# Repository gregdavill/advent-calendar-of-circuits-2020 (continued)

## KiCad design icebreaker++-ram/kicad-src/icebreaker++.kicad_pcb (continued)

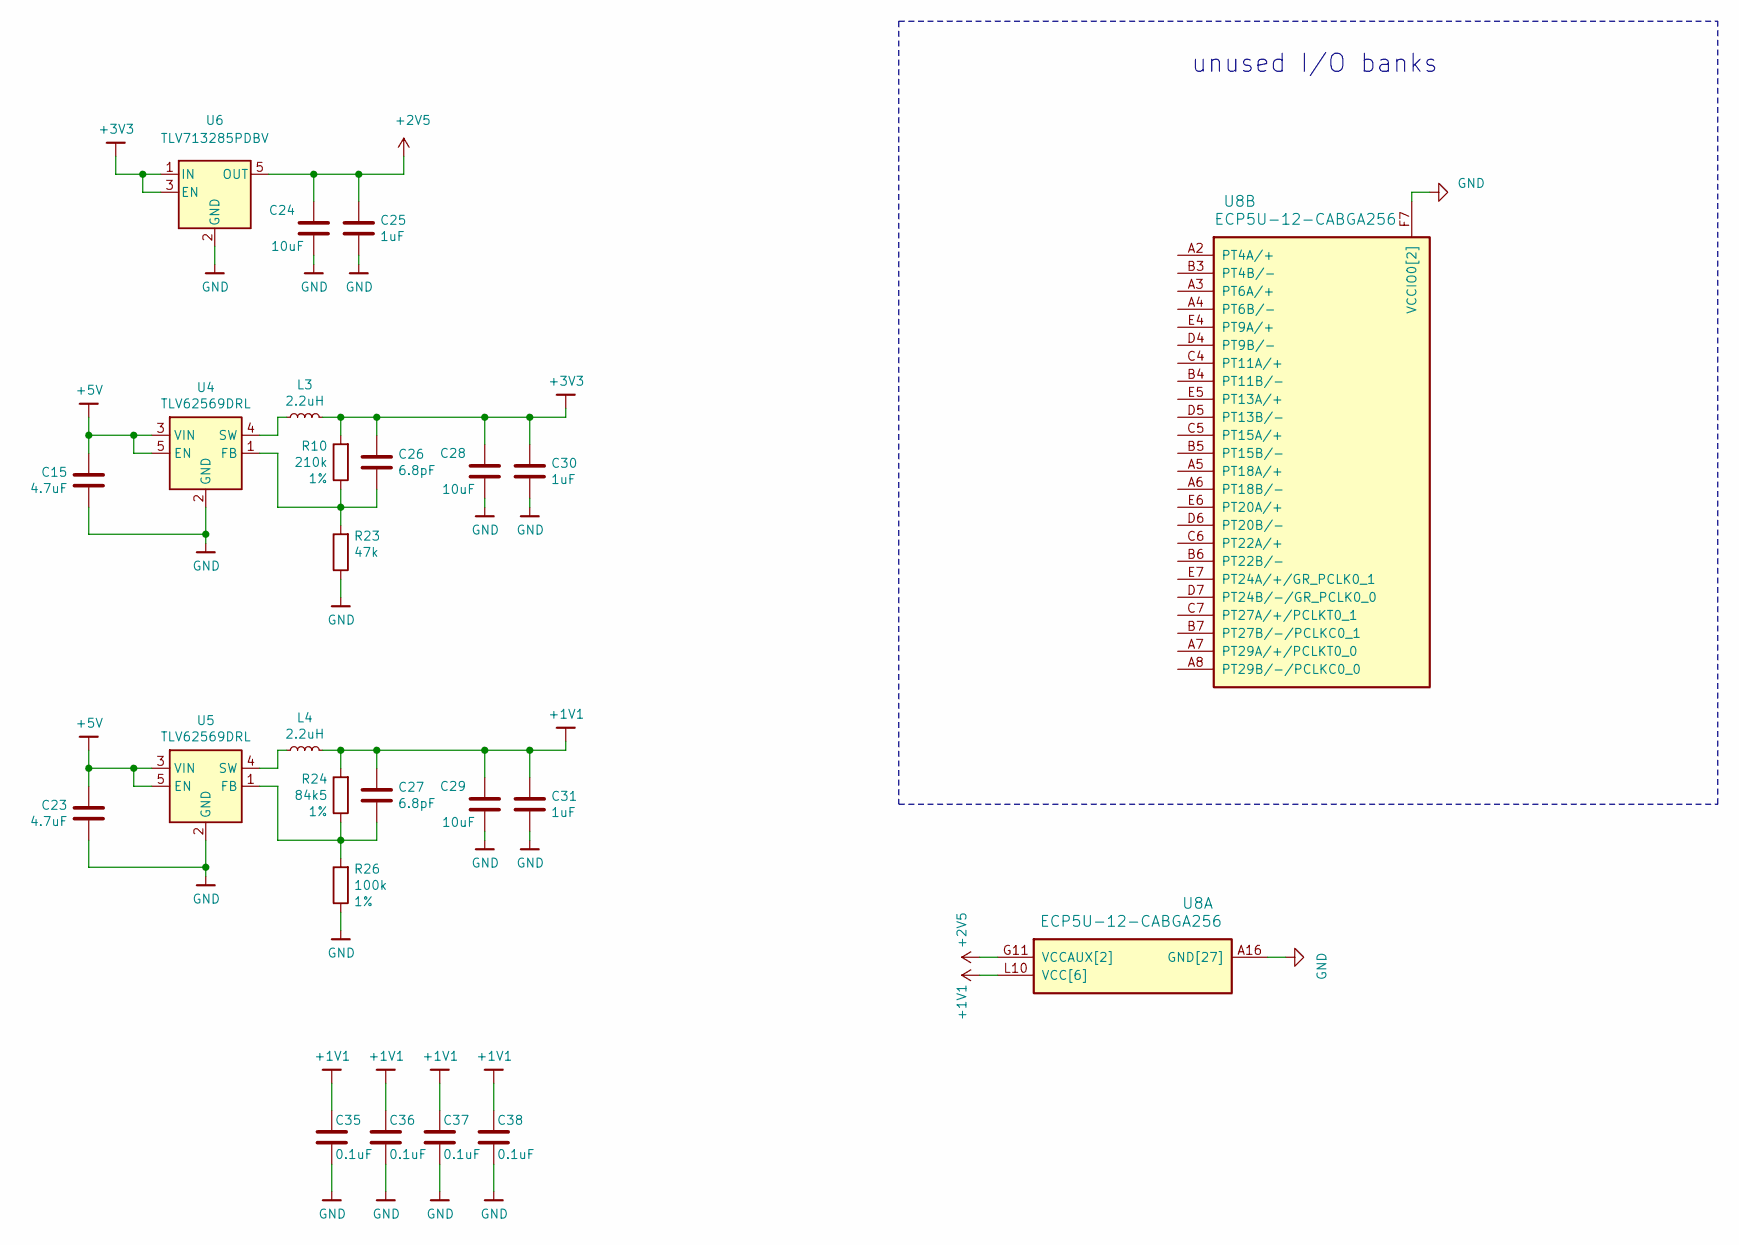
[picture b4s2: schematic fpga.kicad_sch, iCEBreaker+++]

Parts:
C15, C23: 4.7uF; C_0402_1005Metric
C24, C28, C29: 10uF; C_0603_1608Metric
C25, C30, C31: 1uF; C_0402_1005Metric
C26, C27: 6.8pF; C_0402_1005Metric
C35, C36, C37, C38: 0.1uF; C_0402_1005Metric
L3, L4: 2.2uH; L_0805_2012Metric
R10: 210k; R_0402_1005Metric
R23: 47k; R_0402_1005Metric
R24: 84k5; R_0402_1005Metric
R26: 100k; R_0402_1005Metric
U4, U5: TLV62569DRL; SOT-666
U6: TLV713285PDBV; SOT-23-5
U8: ECP5U-12-CABGA256; BGA-256_14.0x14.0mm_Layout16x16_P0.8mm_Ball0.45mm_Pad0.32mm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

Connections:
+1V1: C27.1, C29.1, C31.1, C35.1, C36.1, C37.1, C38.1, L4.2, R24.2, U8.G6 (VCC[6]), U8.G7 (VCC[6]), U8.G9 (VCC[6]), U8.L8 (VCC[6]), U8.L9 (VCC[6]), U8.L10 (VCC[6])
+2V5: C24.1, C25.1, U6.5 (OUT), U8.G11 (VCCAUX[2]), U8.L7 (VCCAUX[2])
+3V3: C26.1, C28.1, C30.1, L3.2, R10.2, U6.1 (IN), U6.3 (EN); also elsewhere on the board
+5V: C15.1, C23.1, U4.3 (VIN), U4.5 (EN), U5.3 (VIN), U5.5 (EN); also elsewhere on the board
GND: C15.2, C23.2, C24.2, C25.2, C28.2, C29.2, C30.2, C31.2, C35.2, C36.2, C37.2, C38.2, R23.1, R26.1, U4.2 (GND), U5.2 (GND), U6.2 (GND), U8.A1 (GND[27]), U8.A16 (GND[27]), U8.D2 (GND[27]), U8.D15 (GND[27]), U8.F6 (VCCIO0[2]), U8.F7 (VCCIO0[2]), U8.F8 (GND[27]), U8.F9 (GND[27]), U8.G8 (GND[27]), U8.G10 (GND[27]), U8.H1 (GND[27]), U8.H8 (GND[27]), U8.H9 (GND[27]), U8.H10 (GND[27]), U8.H16 (GND[27]), U8.J8 (GND[27]), U8.J9 (GND[27]), U8.J10 (GND[27]), U8.K6 (GND[27]), U8.K7 (GND[27]), U8.K8 (GND[27]), U8.K9 (GND[27]), U8.K10 (GND[27]), U8.N2 (GND[27]), U8.N15 (GND[27]), U8.T1 (GND[27]), U8.T5 (GND[27]), U8.T12 (GND[27]), U8.T16 (GND[27]); also elsewhere on the board
unnamed: C26.2, R10.1, R23.2, U4.1 (FB)
unnamed: C27.2, R24.1, R26.2, U5.1 (FB)
unnamed: L3.1, U4.4 (SW)
unnamed: L4.1, U5.4 (SW)
no_connect_283: U4.6 (NC)
no_connect_284: U5.6 (NC)
no_connect_285: U6.4 (NC)

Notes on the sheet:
unused I/O banks

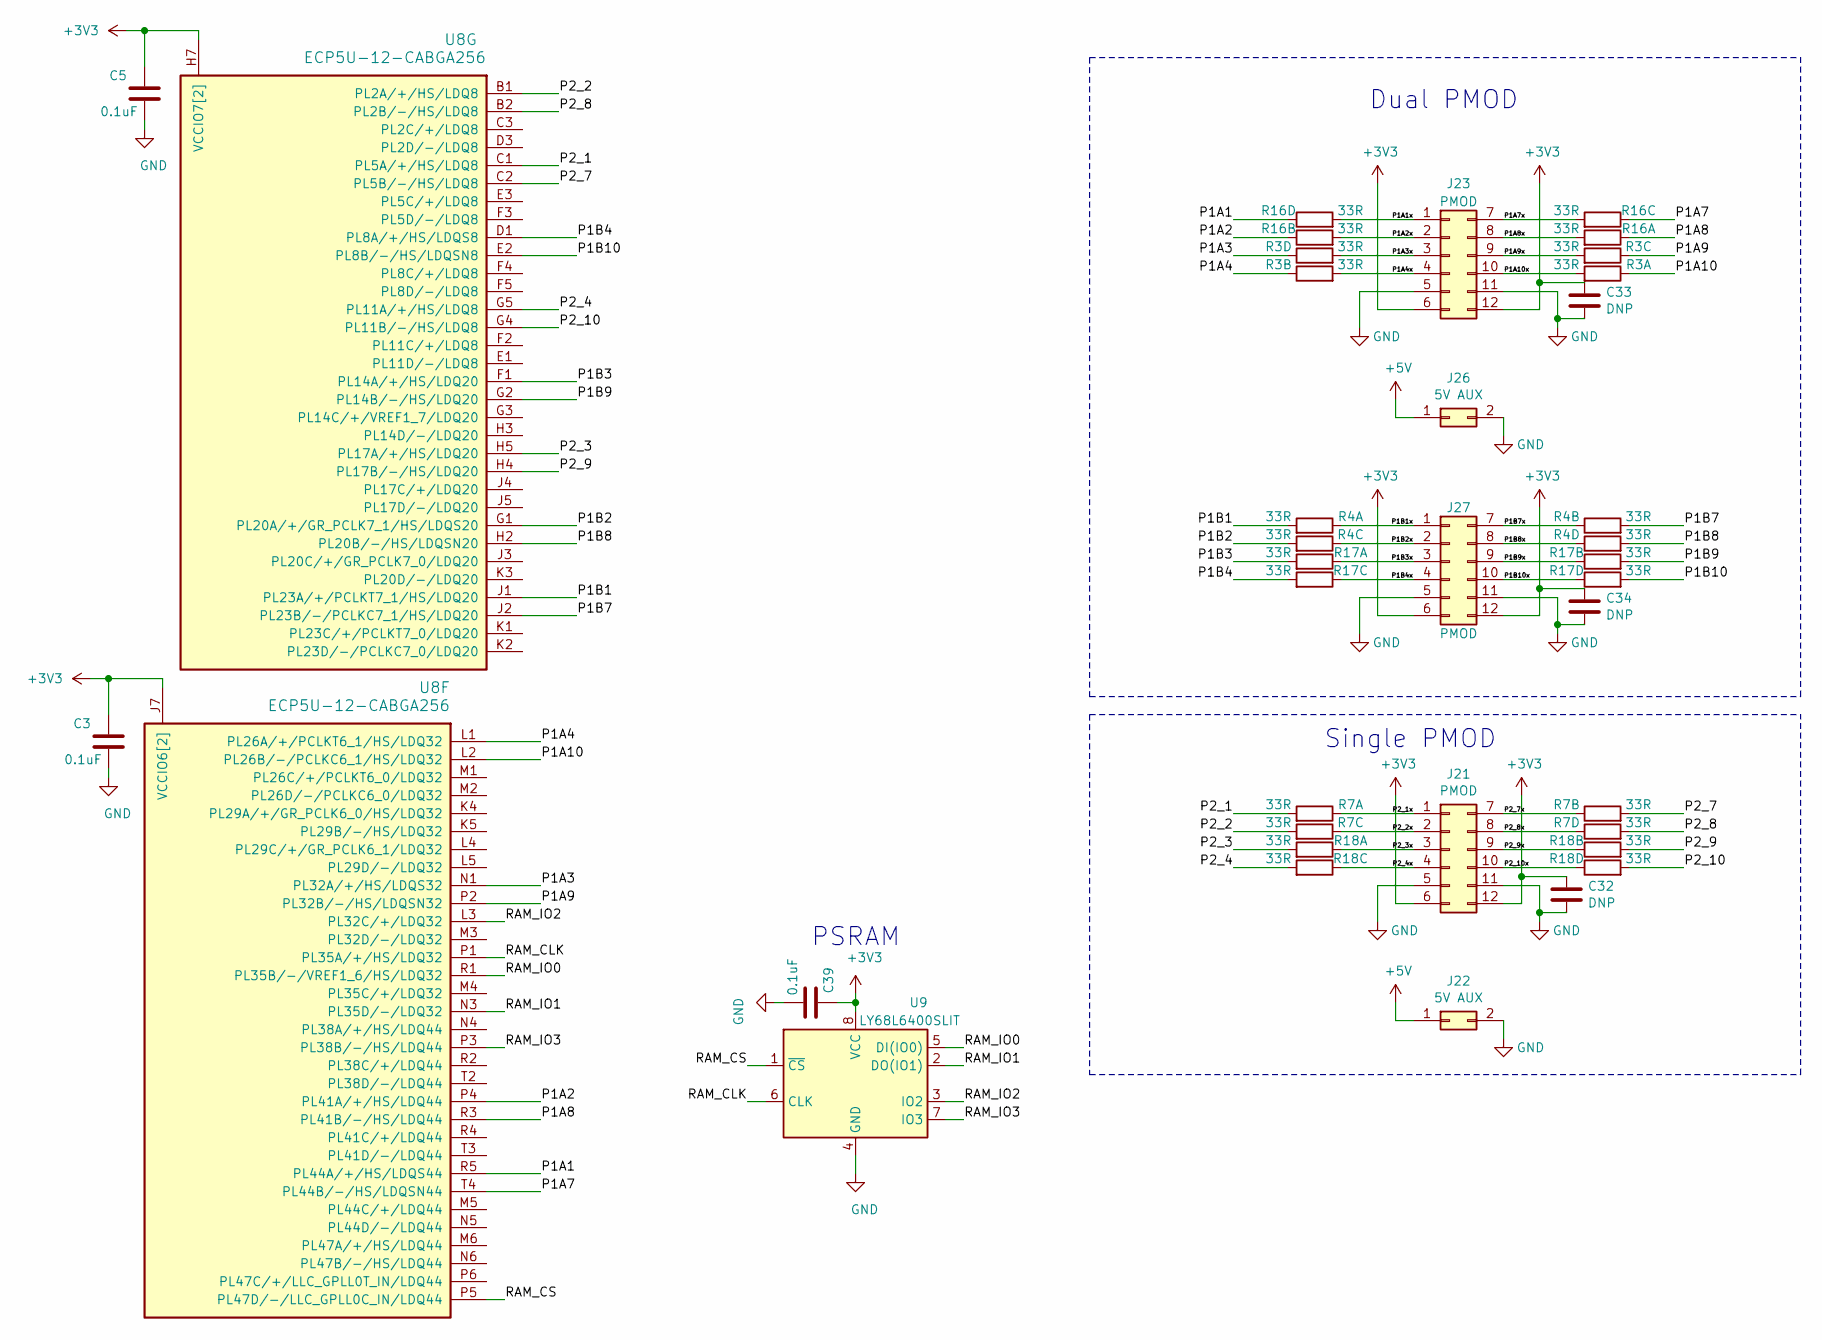
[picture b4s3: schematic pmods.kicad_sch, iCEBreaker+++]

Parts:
C3, C5, C39: 0.1uF; C_0402_1005Metric
C32, C33, C34: DNP; C_0603_1608Metric
J21, J23, J27: PMOD; PMOD_Angled_2x06
J22, J26: 5V AUX; PinHeader_2x01_P2.54mm_Vertical
R3, R4, R7, R16, R17, R18: 33R; R_Array_Convex_4x0402
U8: ECP5U-12-CABGA256; BGA-256_14.0x14.0mm_Layout16x16_P0.8mm_Ball0.45mm_Pad0.32mm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
U9: LY68L6400SLIT; SOIC-8_3.9x4.9mm_P1.27mm

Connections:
+3V3: C3.1, C5.1, C32.2, C33.2, C34.2, C39.1, J21.6, J21.12, J23.6, J23.12, J27.6, J27.12, U8.H6 (VCCIO7[2]), U8.H7 (VCCIO7[2]), U8.J6 (VCCIO6[2]), U8.J7 (VCCIO6[2]), U9.8 (VCC); also elsewhere on the board
+5V: J22.1, J26.1; also elsewhere on the board
/PMODS/P1A1: R16.5, U8.R5 (PL44A/+/HS/LDQS44)
/PMODS/P1A1x: J23.1, R16.4
/PMODS/P1A2: R16.7, U8.P4 (PL41A/+/HS/LDQ44)
/PMODS/P1A2x: J23.2, R16.2
/PMODS/P1A3: R3.5, U8.N1 (PL32A/+/HS/LDQS32)
/PMODS/P1A3x: J23.3, R3.4
/PMODS/P1A4: R3.7, U8.L1 (PL26A/+/PCLKT6_1/HS/LDQ32)
/PMODS/P1A4x: J23.4, R3.2
/PMODS/P1A7: R16.6, U8.T4 (PL44B/-/HS/LDQSN44)
/PMODS/P1A7x: J23.7, R16.3
/PMODS/P1A8: R16.8, U8.R3 (PL41B/-/HS/LDQ44)
/PMODS/P1A8x: J23.8, R16.1
/PMODS/P1A9: R3.6, U8.P2 (PL32B/-/HS/LDQSN32)
/PMODS/P1A9x: J23.9, R3.3
/PMODS/P1A10: R3.8, U8.L2 (PL26B/-/PCLKC6_1/HS/LDQ32)
/PMODS/P1A10x: J23.10, R3.1
/PMODS/P1B1: R4.1, U8.J1 (PL23A/+/PCLKT7_1/HS/LDQ20)
/PMODS/P1B1x: J27.1, R4.8
/PMODS/P1B2: R4.3, U8.G1 (PL20A/+/GR_PCLK7_1/HS/LDQS20)
/PMODS/P1B2x: J27.2, R4.6
/PMODS/P1B3: R17.1, U8.F1 (PL14A/+/HS/LDQ20)
/PMODS/P1B3x: J27.3, R17.8
/PMODS/P1B4: R17.3, U8.D1 (PL8A/+/HS/LDQS8)
/PMODS/P1B4x: J27.4, R17.6
/PMODS/P1B7: R4.2, U8.J2 (PL23B/-/PCLKC7_1/HS/LDQ20)
/PMODS/P1B7x: J27.7, R4.7
/PMODS/P1B8: R4.4, U8.H2 (PL20B/-/HS/LDQSN20)
/PMODS/P1B8x: J27.8, R4.5
/PMODS/P1B9: R17.2, U8.G2 (PL14B/-/HS/LDQ20)
/PMODS/P1B9x: J27.9, R17.7
/PMODS/P1B10: R17.4, U8.E2 (PL8B/-/HS/LDQSN8)
/PMODS/P1B10x: J27.10, R17.5
/PMODS/P2_1: R7.1, U8.C1 (PL5A/+/HS/LDQ8)
/PMODS/P2_1x: J21.1, R7.8
/PMODS/P2_2: R7.3, U8.B1 (PL2A/+/HS/LDQ8)
/PMODS/P2_2x: J21.2, R7.6
/PMODS/P2_3: R18.1, U8.H5 (PL17A/+/HS/LDQ20)
/PMODS/P2_3x: J21.3, R18.8
/PMODS/P2_4: R18.3, U8.G5 (PL11A/+/HS/LDQ8)
/PMODS/P2_4x: J21.4, R18.6
/PMODS/P2_7: R7.2, U8.C2 (PL5B/-/HS/LDQ8)
/PMODS/P2_7x: J21.7, R7.7
/PMODS/P2_8: R7.4, U8.B2 (PL2B/-/HS/LDQ8)
/PMODS/P2_8x: J21.8, R7.5
/PMODS/P2_9: R18.2, U8.H4 (PL17B/-/HS/LDQ20)
/PMODS/P2_9x: J21.9, R18.7
/PMODS/P2_10: R18.4, U8.G4 (PL11B/-/HS/LDQ8)
/PMODS/P2_10x: J21.10, R18.5
/PMODS/RAM_CLK: U8.P1 (PL35A/+/HS/LDQ32), U9.6 (CLK)
/PMODS/RAM_CS: U8.P5 (PL47D/-/LLC_GPLL0C_IN/LDQ44), U9.1 (~CS)
/PMODS/RAM_IO0: U8.R1 (PL35B/-/VREF1_6/HS/LDQ32), U9.5 (DI(IO0))
/PMODS/RAM_IO1: U8.N3 (PL35D/-/LDQ32), U9.2 (DO(IO1))
/PMODS/RAM_IO2: U8.L3 (PL32C/+/LDQ32), U9.3 (IO2)
/PMODS/RAM_IO3: U8.P3 (PL38B/-/HS/LDQ44), U9.7 (IO3)
GND: C3.2, C5.2, C32.1, C33.1, C34.1, C39.2, J21.5, J21.11, J22.2, J23.5, J23.11, J26.2, J27.5, J27.11, U9.4 (GND); also elsewhere on the board

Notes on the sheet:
PSRAM
Single PMOD
Dual PMOD

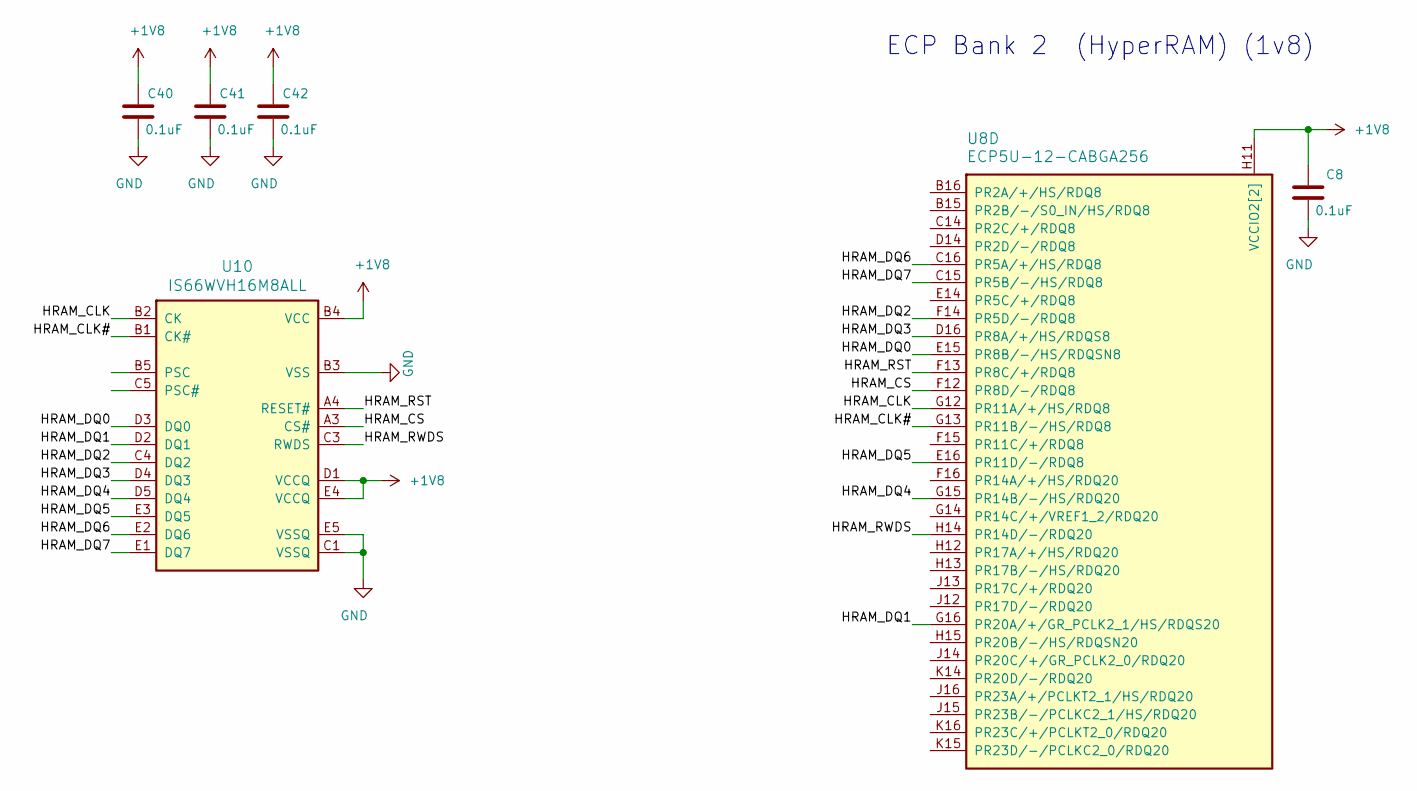
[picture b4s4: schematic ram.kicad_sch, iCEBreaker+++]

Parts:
C8, C40, C41, C42: 0.1uF; C_0402_1005Metric
U8: ECP5U-12-CABGA256; BGA-256_14.0x14.0mm_Layout16x16_P0.8mm_Ball0.45mm_Pad0.32mm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
U10: IS66WVH16M8ALL; BGA-24_8.0x6.0mm_Layout5x5_P0.8mm_Pad0.35mm_NSMD

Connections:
+1V8: C8.1, C40.1, C41.1, C42.1, U8.H11 (VCCIO2[2]), U8.J11 (VCCIO2[2]), U10.B4 (VCC), U10.D1 (VCCQ), U10.E4 (VCCQ); also elsewhere on the board
/RAM/HRAM_CLK: U8.G12 (PR11A/+/HS/RDQ8), U10.B2 (CK)
/RAM/HRAM_CLK#: U8.G13 (PR11B/-/HS/RDQ8), U10.B1 (CK#)
/RAM/HRAM_CS: U8.F12 (PR8D/-/RDQ8), U10.A3 (CS#)
/RAM/HRAM_DQ0: U8.E15 (PR8B/-/HS/RDQSN8), U10.D3 (DQ0)
/RAM/HRAM_DQ1: U8.G16 (PR20A/+/GR_PCLK2_1/HS/RDQS20), U10.D2 (DQ1)
/RAM/HRAM_DQ2: U8.F14 (PR5D/-/RDQ8), U10.C4 (DQ2)
/RAM/HRAM_DQ3: U8.D16 (PR8A/+/HS/RDQS8), U10.D4 (DQ3)
/RAM/HRAM_DQ4: U8.G15 (PR14B/-/HS/RDQ20), U10.D5 (DQ4)
/RAM/HRAM_DQ5: U8.E16 (PR11D/-/RDQ8), U10.E3 (DQ5)
/RAM/HRAM_DQ6: U8.C16 (PR5A/+/HS/RDQ8), U10.E2 (DQ6)
/RAM/HRAM_DQ7: U8.C15 (PR5B/-/HS/RDQ8), U10.E1 (DQ7)
/RAM/HRAM_RST: U8.F13 (PR8C/+/RDQ8), U10.A4 (RESET#)
/RAM/HRAM_RWDS: U8.H14 (PR14D/-/RDQ20), U10.C3 (RWDS)
GND: C8.2, C40.2, C41.2, C42.2, U10.B3 (VSS), U10.C1 (VSSQ), U10.E5 (VSSQ); also elsewhere on the board

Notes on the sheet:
ECP Bank 2 (HyperRAM) (1v8)

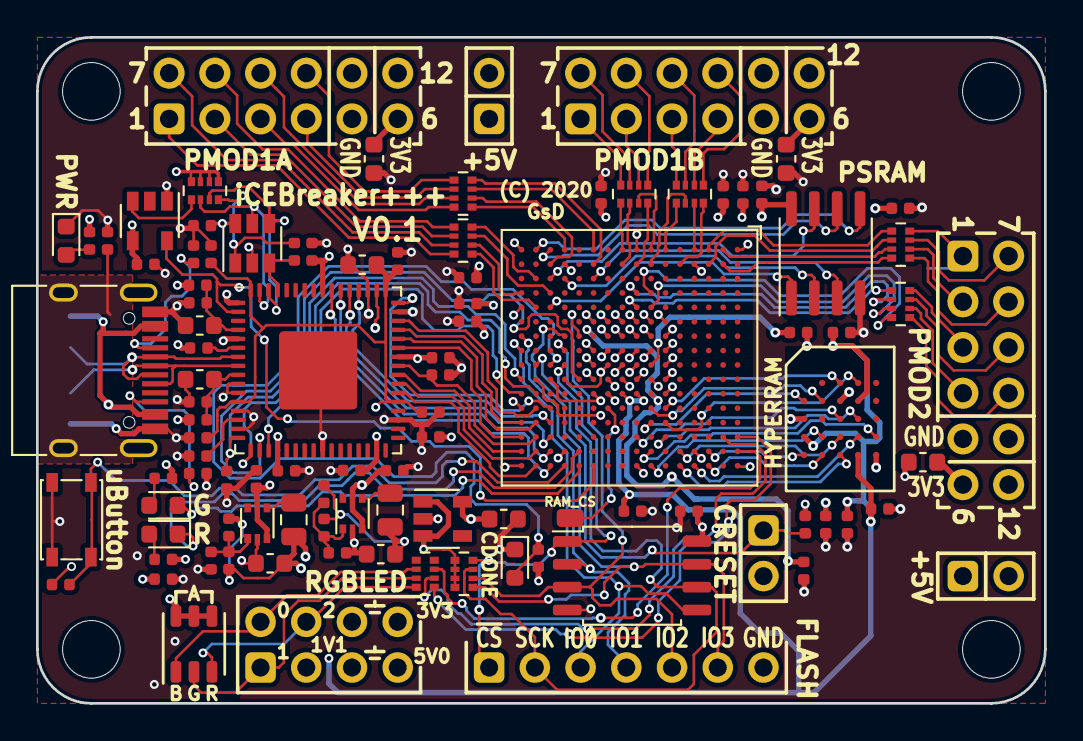
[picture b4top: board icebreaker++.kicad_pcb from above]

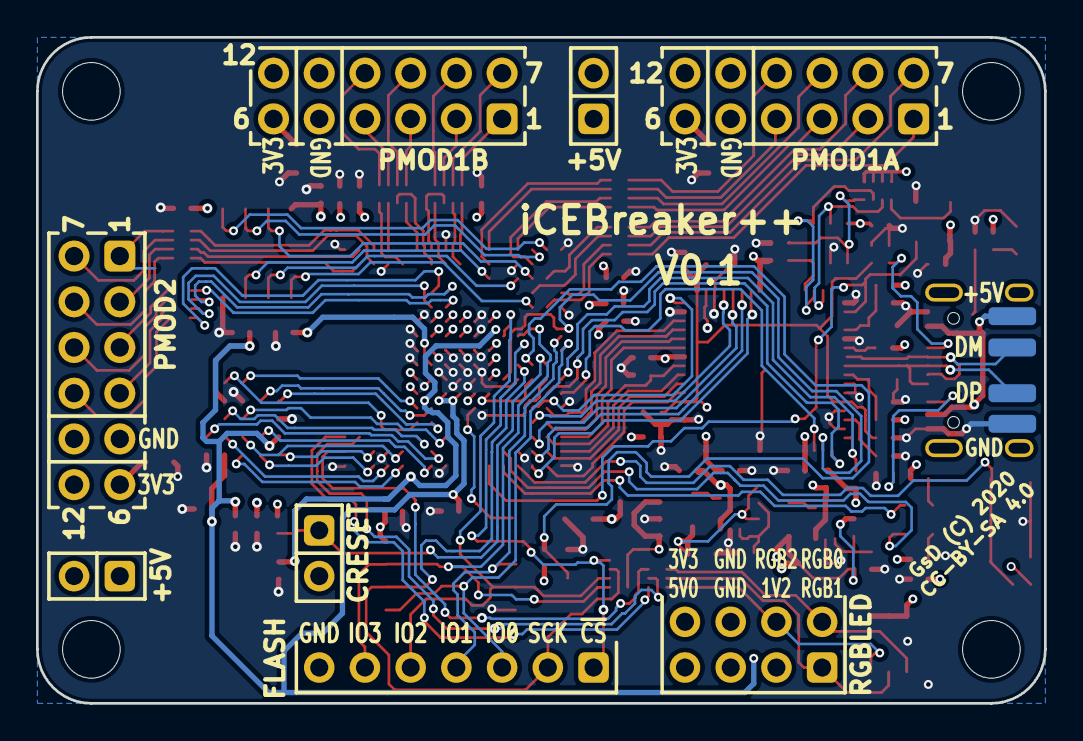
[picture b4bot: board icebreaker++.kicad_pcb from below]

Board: 4 copper layers, 56.0 x 37.0 mm, 104 parts (4 on the bottom side), 130 nets.

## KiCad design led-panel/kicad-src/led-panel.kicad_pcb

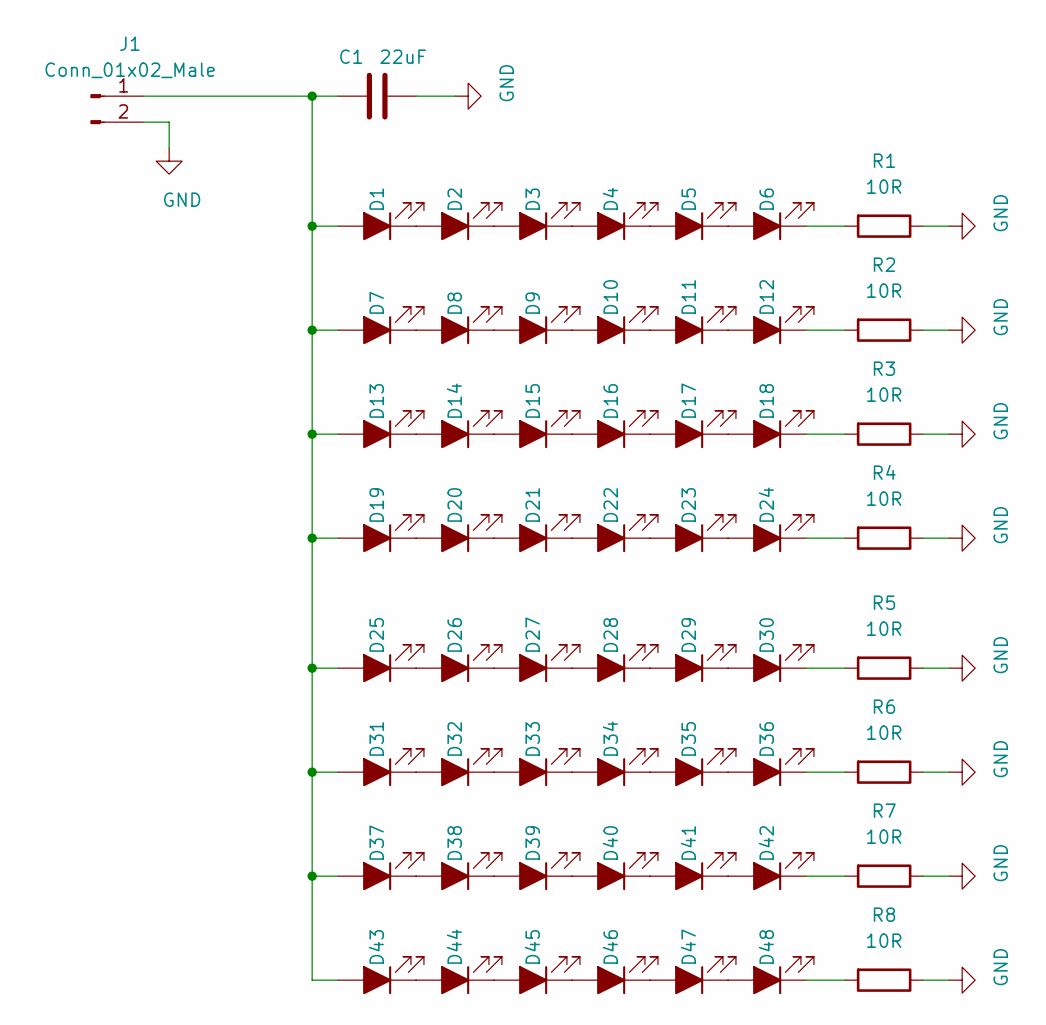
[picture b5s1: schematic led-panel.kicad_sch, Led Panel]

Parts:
C1: 22uF; C_1210_3225Metric
D1, D2, D3, D4, D5, D6, D7, D8, D9, D10, D11, D12, D13, D14, D15, D16, D17, D18, D19, D20, D21, D22, D23, D24, D25, D26, D27, D28, D29, D30, D31, D32, D33, D34, D35, D36, D37, D38, D39, D40, D41, D42, D43, D44, D45, D46, D47, D48: LED_ALT; LED_LUXEON_3014
J1: Conn_01x02_Male; PinHeader_1x02_P2.54mm_Horizontal
R1, R2, R3, R4, R5, R6, R7, R8: 10R; R_0603_1608Metric

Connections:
GND: C1.2, J1.2, R1.1, R2.1, R3.1, R4.1, R5.1, R6.1, R7.1, R8.1
unnamed: C1.1, D1.2 (A), D7.2 (A), D13.2 (A), D19.2 (A), D25.2 (A), D31.2 (A), D37.2 (A), D43.2 (A), J1.1
unnamed: D1.1 (K), D2.2 (A)
unnamed: D2.1 (K), D3.2 (A)
unnamed: D3.1 (K), D4.2 (A)
unnamed: D4.1 (K), D5.2 (A)
unnamed: D5.1 (K), D6.2 (A)
unnamed: D6.1 (K), R1.2
unnamed: D7.1 (K), D8.2 (A)
unnamed: D8.1 (K), D9.2 (A)
unnamed: D10.1 (K), D11.2 (A)
unnamed: D9.1 (K), D10.2 (A)
unnamed: D11.1 (K), D12.2 (A)
unnamed: D12.1 (K), R2.2
unnamed: D13.1 (K), D14.2 (A)
unnamed: D14.1 (K), D15.2 (A)
unnamed: D15.1 (K), D16.2 (A)
unnamed: D16.1 (K), D17.2 (A)
unnamed: D17.1 (K), D18.2 (A)
unnamed: D18.1 (K), R3.2
unnamed: D19.1 (K), D20.2 (A)
unnamed: D20.1 (K), D21.2 (A)
unnamed: D21.1 (K), D22.2 (A)
unnamed: D22.1 (K), D23.2 (A)
unnamed: D23.1 (K), D24.2 (A)
unnamed: D24.1 (K), R4.2
unnamed: D25.1 (K), D26.2 (A)
unnamed: D26.1 (K), D27.2 (A)
unnamed: D27.1 (K), D28.2 (A)
unnamed: D28.1 (K), D29.2 (A)
unnamed: D29.1 (K), D30.2 (A)
unnamed: D30.1 (K), R5.2
unnamed: D31.1 (K), D32.2 (A)
unnamed: D32.1 (K), D33.2 (A)
unnamed: D33.1 (K), D34.2 (A)
unnamed: D34.1 (K), D35.2 (A)
unnamed: D35.1 (K), D36.2 (A)
unnamed: D36.1 (K), R6.2
unnamed: D37.1 (K), D38.2 (A)
unnamed: D38.1 (K), D39.2 (A)
unnamed: D39.1 (K), D40.2 (A)
unnamed: D40.1 (K), D41.2 (A)
unnamed: D41.1 (K), D42.2 (A)
unnamed: D42.1 (K), R7.2
unnamed: D43.1 (K), D44.2 (A)
unnamed: D44.1 (K), D45.2 (A)
unnamed: D45.1 (K), D46.2 (A)
unnamed: D46.1 (K), D47.2 (A)
unnamed: D47.1 (K), D48.2 (A)
unnamed: D48.1 (K), R8.2

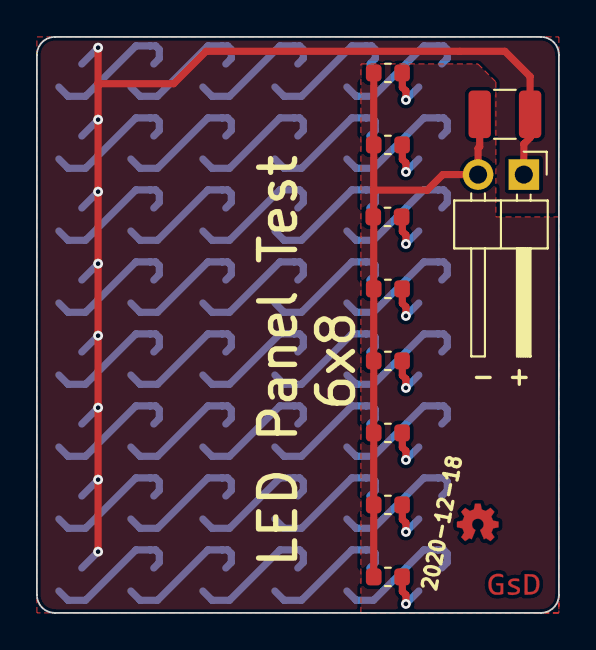
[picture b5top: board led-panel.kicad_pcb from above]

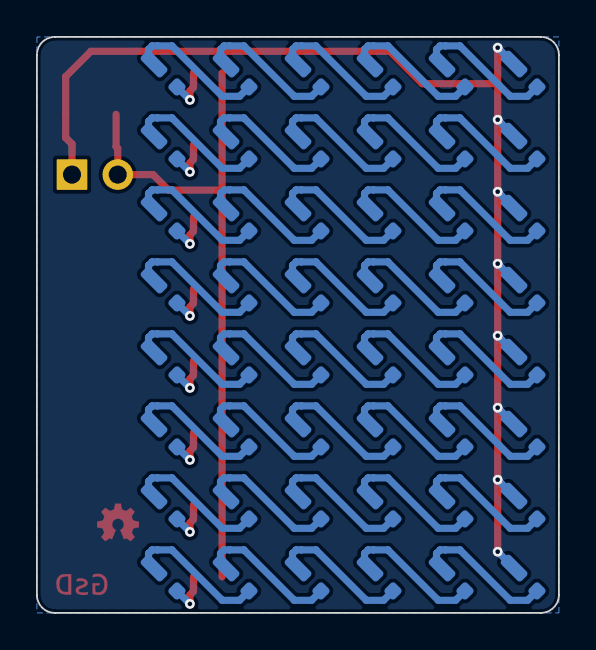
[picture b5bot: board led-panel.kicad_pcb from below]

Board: 2 copper layers, 29.0 x 32.0 mm, 58 parts (48 on the bottom side), 50 nets.

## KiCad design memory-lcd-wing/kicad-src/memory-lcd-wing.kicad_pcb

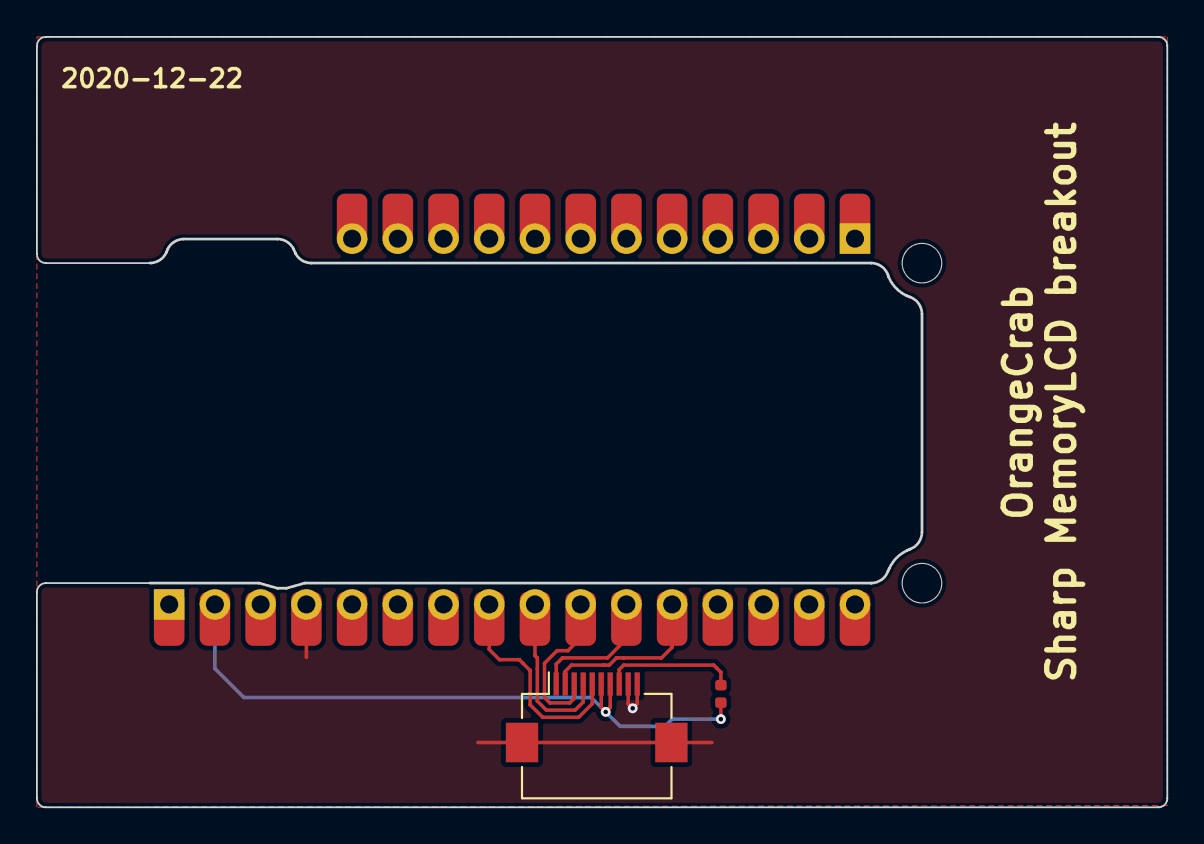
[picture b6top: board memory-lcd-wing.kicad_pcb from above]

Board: 2 copper layers, 62.8 x 42.8 mm, 4 parts (0 on the bottom side), 8 nets.

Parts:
J1: Conn_01x16; PinHeader_1x16_P2.54mm_Vertical
J2: Conn_01x12; PinHeader_1x12_P2.54mm_Vertical
J3: Conn_01x10_MountingPin; Hirose_FH12-10S-0.5SH_1x10-1MP_P0.50mm_Horizontal
R1: 0R; R_0402_1005Metric

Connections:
+3V3: J1.2, J3.6, J3.7, R1.1
/DISP: J1.8, J3.5
/EXTCOMIN: J1.9, J3.4
/EXTMODE: J3.8, R1.2
/SCS: J1.10, J3.3
/mo: J1.12, J3.2
/sck: J1.11, J3.1
GND: J1.4, J3.9, J3.10, J3.MP (MountPin)

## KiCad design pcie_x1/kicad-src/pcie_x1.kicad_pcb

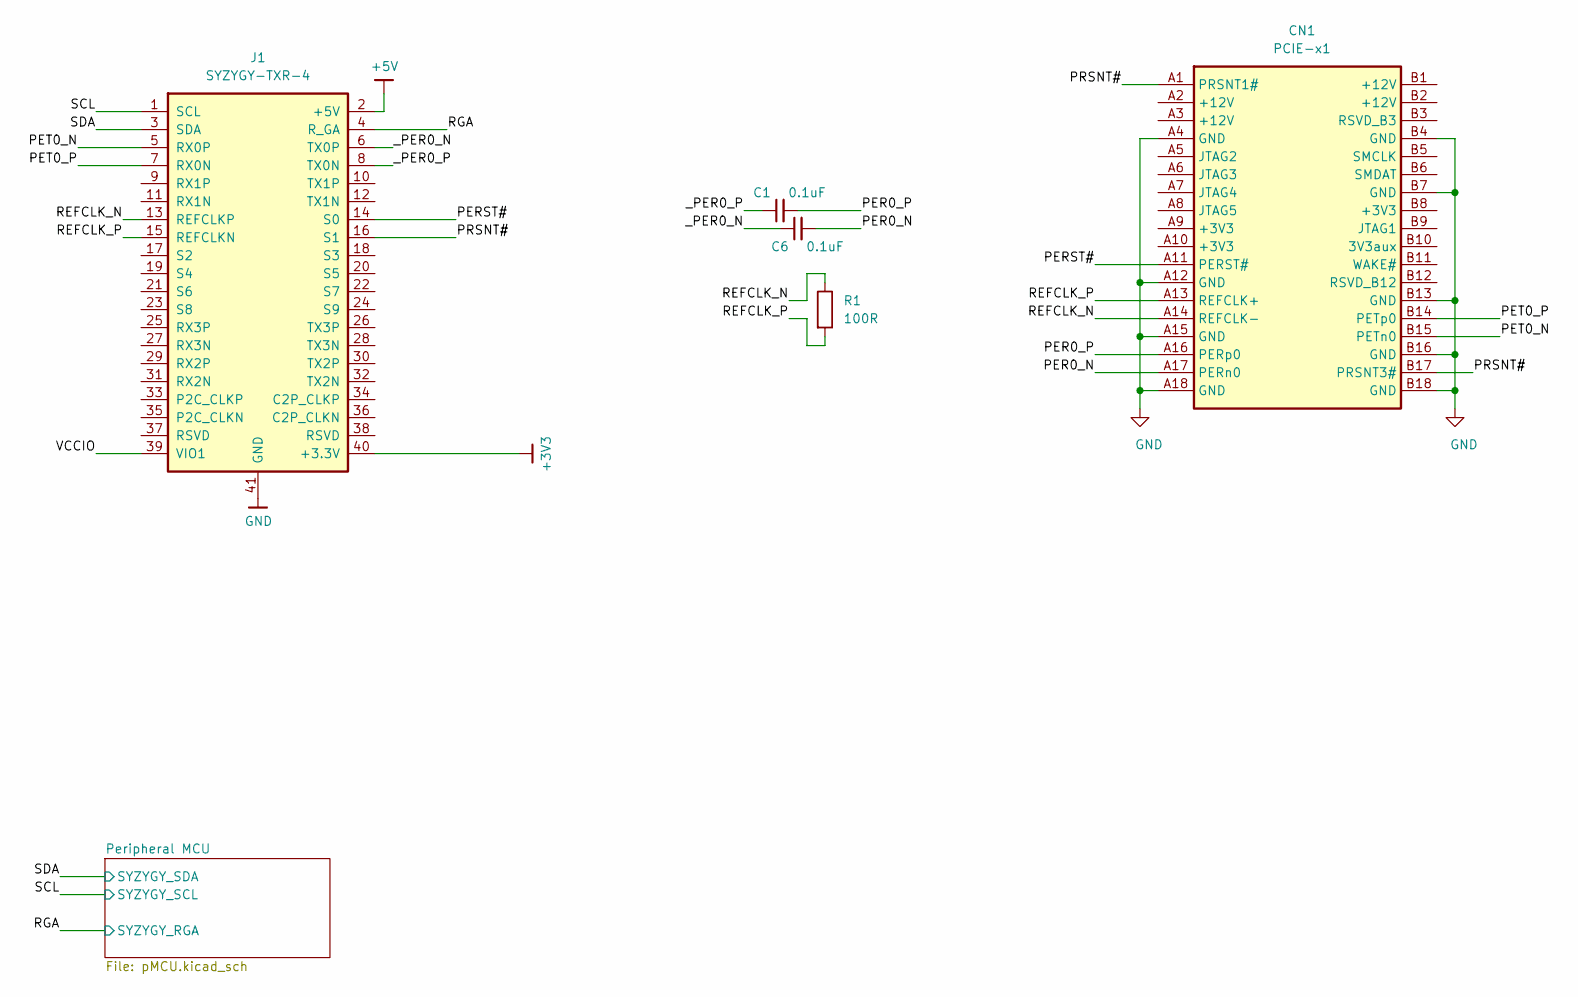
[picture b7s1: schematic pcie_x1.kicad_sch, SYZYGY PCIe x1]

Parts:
C1, C6: 0.1uF; C_0402_1005Metric
CN1: PCIE-x1; BUS_PCIexpress_x1
J1: SYZYGY-TXR-4; SYZYGY-TXR-POD
R1: 100R; R_0402_1005Metric

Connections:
+3V3: J1.40 (+3.3V); also elsewhere on the board
+5V: J1.2 (+5V)
/PER0_N: C6.2, CN1.A17 (PERn0)
/PER0_P: C1.2, CN1.A16 (PERp0)
/PERST#: CN1.A11 (PERST#), J1.14 (S0)
/PET0_N: CN1.B15 (PETn0), J1.5 (RX0P)
/PET0_P: CN1.B14 (PETp0), J1.7 (RX0N)
/PRSNT#: CN1.A1 (PRSNT1#), CN1.B17 (PRSNT3#), J1.16 (S1)
/REFCLK_N: CN1.A14 (REFCLK-), J1.13 (REFCLKP), R1.1
/REFCLK_P: CN1.A13 (REFCLK+), J1.15 (REFCLKN), R1.2
/RGA: J1.4 (R_GA); also elsewhere on the board
/SCL: J1.1 (SCL); also elsewhere on the board
/SDA: J1.3 (SDA); also elsewhere on the board
/VCCIO: J1.39 (VIO1)
/_PER0_N: C6.1, J1.6 (TX0P)
/_PER0_P: C1.1, J1.8 (TX0N)
GND: CN1.A4 (GND), CN1.A12 (GND), CN1.A15 (GND), CN1.A18 (GND), CN1.B4 (GND), CN1.B7 (GND), CN1.B13 (GND), CN1.B16 (GND), CN1.B18 (GND), J1.41 (GND); also elsewhere on the board

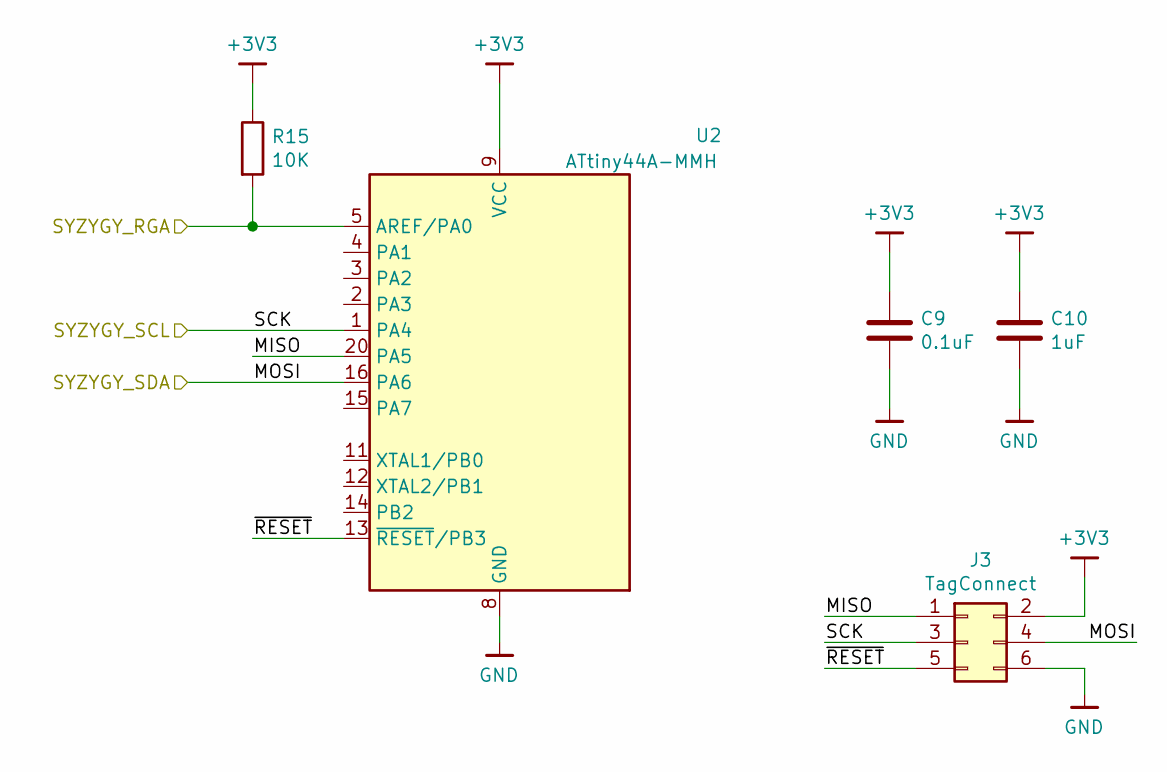
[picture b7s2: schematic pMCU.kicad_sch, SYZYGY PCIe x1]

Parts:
C9: 0.1uF; C_0402_1005Metric
C10: 1uF; C_0402_1005Metric
J3: TagConnect; TC2030-NL_SMALL
R15: 10K; R_0402_1005Metric
U2: ATtiny44A-MMH; QFN-20-1EP_3x3mm_P0.45mm_EP1.6x1.6mm

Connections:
+3V3: C9.1, C10.1, J3.2, R15.1, U2.9 (VCC); also elsewhere on the board
/Peripheral MCU/MISO: J3.1, U2.20 (PA5)
/Peripheral MCU/~RESET: J3.5, U2.13 (~RESET~/PB3)
/RGA: R15.2, U2.5 (AREF/PA0); also elsewhere on the board
/SCL: J3.3, U2.1 (PA4); also elsewhere on the board
/SDA: J3.4, U2.16 (PA6); also elsewhere on the board
GND: C9.2, C10.2, J3.6, U2.8 (GND), U2.21 (GND); also elsewhere on the board

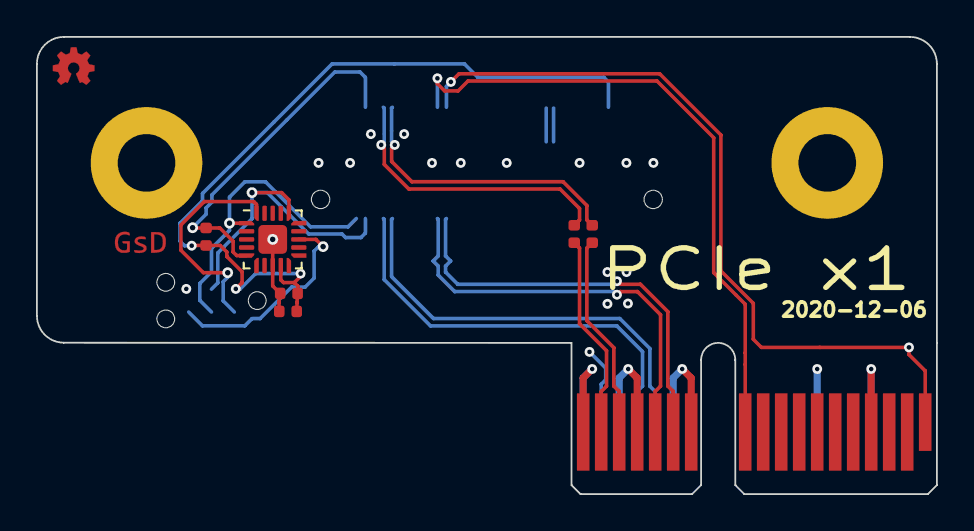
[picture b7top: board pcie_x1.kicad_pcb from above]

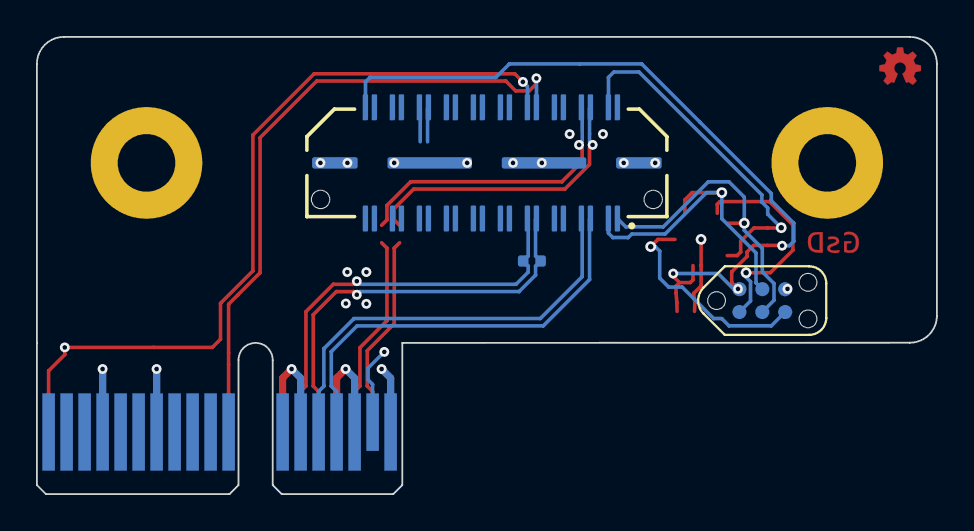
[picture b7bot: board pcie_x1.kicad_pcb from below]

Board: 4 copper layers, 50.0 x 25.4 mm, 10 parts (4 on the bottom side), 17 nets.
